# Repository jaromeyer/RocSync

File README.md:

# 🎥 RocSync
 
**Millisecond-Accurate Temporal Synchronization for Heterogeneous Camera Systems**

> *Jaro Meyer¹, Frédéric Giraud², Joschua Wüthrich¹, Marc Pollefeys¹, Philipp Fürnstahl², Lilian Calvet²*
>
> ¹ Department of Computer Science, ETH Zurich, Switzerland\
> ² Research in Orthopedic Computer Science, Balgrist University Hospital, University of Zurich, Switzerland

> [!WARNING]
> **This repository is deprecated and no longer maintained.**
> Development has moved to a new fork, which will continue to be updated:
> 👉 **[BAL-ROCS-BUT-COOL/RocSync](https://github.com/BAL-ROCS-BUT-COOL/RocSync)**

**RocSync**  is an open-source solution for millisecond-accurate temporal synchronization of multiple cameras. The core component is a 25x25 cm PCB featuring 100 dual LEDs (each consisting of a visible red LED and an infrared LED) arranged in a circle and 16 additional dual LEDs to display a binary counter. There is always exactly one illuminated LED in the circle and it advances one step every millisecond, while the binary display counts the number of complete rotations. The second part is a Python application that decodes images and videos of the device and provides exact timestamps (relative to the RocSync device's internal clock) for every frame. It supports synchronization of both standard RGB cameras (e.g., Kinect, GoPro, Canon) and specialized IR tracking cameras, such as the [Atracsys fusionTrack 500](https://atracsys.com/fusiontrack-500/), making it ideal for research and applications requiring high-precision multi-camera setups.

## Repository Structure

This repository contains three main sections, each with its own README:

- **`fw/`**: PlatformIO project for microcontroller firmware.
- **`hw/`**: KiCad files for PCB design and CAD models.
- **`misc/`**: IR marker geometry specifications.
- **`sw/`**: Python source code for computer vision processing.

## Getting Started

For detailed instructions on setting up and using RocSync, please refer to the README files in the respective sections.

## Citation
If you use RocSync in your research, please cite:
```
@Article{s26031036,
AUTHOR = {Meyer, Jaro and Giraud, Frédéric and Wüthrich, Joschua and Pollefeys, Marc and Fürnstahl, Philipp and Calvet, Lilian},
TITLE = {RocSync: Millisecond-Accurate Temporal Synchronization for Heterogeneous Camera Systems},
JOURNAL = {Sensors},
VOLUME = {26},
YEAR = {2026},
NUMBER = {3},
ARTICLE-NUMBER = {1036},
URL = {https://www.mdpi.com/1424-8220/26/3/1036},
PubMedID = {41682551},
ISSN = {1424-8220},
DOI = {10.3390/s26031036}
}
```

## Credits

- **Frédéric Giraud**: Creator of the initial prototype.
- **Lilian Calvet**: Conceptual designer.

Feel free to explore, contribute, and use RocSync in your projects!

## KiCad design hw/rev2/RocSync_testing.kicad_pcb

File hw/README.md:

# RocSync Hardware
This folder contains the KiCad project for the RocSync device, designed with JLCPCB manufacturing and assembly in mind. Fabrication files were generated using the [JLCPCB tools plugin](https://github.com/Bouni/kicad-jlcpcb-tools). The latest production files are available [here](rev2/jlcpcb/production_files/).

## Accuracy
Revision 1 likely experienced accuracy issues documented [here](https://github.com/nlouman/documentation_todos_nino/blob/main/rocsync/1_checking_rocsync_clock.md), though never confirmed against a known accurate reference. Revision 2 replaced the crystal with a high-precision TCXO to improve absolute accuracy. Testing against a u-blox NEO-M8N GPS timepulse output showed ~1.3 ppm drift over 24 hours, roughly consistent with the TCXO's specification. This equates to 1 ms drift every 13 minutes. 

For even better accuracy, consider dedicating an unused GPIO pin (e.g., OLED SDA or SCL) to feed a 1000 Hz timepulse signal directly from the GPS module into the microcontroller, using it as the clock source.

## Revision History
- **Rev1**: Initial design with 16-bit counter and crystal oscillator. Single-sided JLCPCB assembly with manual back-side soldering.
- **Rev2**: Improved design featuring a 20-bit counter, high-precision TCXO, 5-way button interface, and fifth corner LED for unambiguous orientation detection. Optimized for dual-sided assembly.

## Potential Improvements
- [ ] Decouple IR and visible LED brightness
- [ ] Address LED brightness degradation at low battery voltage (consider implementing a buck-boost converter)

## JLCPCB Ordering
1. Upload the **Gerber files** and let JLCPCB auto-populate all options.
2. Enable **PCB Assembly**, selecting **Standard PCBA** and **top side assembly**.
3. Upload the **BOM** and **POS files**.
4. Review the 3D preview and proceed to place your order.

## Mechanical BOM
| Part                                | Quantity | Source                                                              |
| ----------------------------------- | -------- | ------------------------------------------------------------------- |
| 604050 battery with PH2.0 connector | 1        | [Aliexpress](https://aliexpress.com/item/1005009787566737.html) or [Aliexpress](https://aliexpress.com/item/1005010639629430.html) |
| Handle                              | 1        | [3D printed](rev2/3d_models/handle.stl)                             |
| Cover                               | 1        | [3D printed](rev2/3d_models/top_cover.stl)                          |
| M3x10 screws                        | 4        | [Aliexpress](https://www.aliexpress.com/item/32850409234.html)      |
| M3 nuts                             | 4        | [Aliexpress](https://www.aliexpress.com/item/32977174437.html)      |
| Matte smoked film ~32x32 cm         | 1        | [Aliexpress](https://www.aliexpress.com/item/1005005636607163.html) |

## Assembly Instructions
> ⚠️ **Warning**: Verify battery polarity before turning on! The polarity of PH2.0 connectors may differ among battery manufacturers. The positive pin should be the one located closer to the center of the device. 

1. **Prepare the Film**  
   Cut a **30x30 cm square** from the matte smoked film. Place it with the **sticky side facing up** on a flat surface.

2. **Position the Faceplate**  
   Carefully center the **3D printed faceplate** on the film, ensuring the side with the **cutouts** that will later contact the PCB is facing up. If the film is curling, it can be helpful to have someone hold down the corners of the film while you position the faceplate.

3. **Create Center Flaps**  
   Use a cutter or knife to make an **X-shaped cut** in the center square hole of the film. Fold the resulting four flaps upwards and trim the tips, leaving a **2-3 cm strip**. Stick them to the faceplate, making sure to tension the film for a tight fit around the cutout.

4. **Clear Cutouts**  
   Cut away the film from the **cutouts** by slicing along their edges to detach the small film pieces. For the **top side** with **40 counter LEDs**, consider cutting the film into vertical strips between the LEDs and removing the sections covering the LEDs, rather than cutting out each hole individually.

5. **Attach the PCB**  
   Place the **PCB** facing down onto the prepared front plate, ensuring all LEDs are protruding through the cutouts. The PCB should fit snugly against the faceplate.

6. **Secure the PCB**  
    Cut away squares from the outer corners of the film to create flaps that can be folded around the PCB and adhered to its back. This will hold the PCB tightly against the faceplate. Make sure to firmly pull the film around the edge before sticking it down. It is easiest to start from the **middle** and work your way out to the corners, pulling the film tight each time before adhering a new section to the PCB.

7. **Attach the Handle**
   Use a cutter to poke holes through the film for the **four screws**. Attach the handle to the back of the PCB, ensuring the **battery cable** routes through the designated channel, and secure it with screws and nuts.

8. **Secure the Battery**  
   Adhere the battery to the back of the handle using **thin double-sided tape** to prevent it from falling out when the device is turned upside down. If the battery doesn't fit directly, you might have to fold its corners inwards to make it fit.

9.  **Connect the Battery and Power On**  
    Connect the battery to the PCB, ensuring the **correct polarity**. The positive pin should be the one closer to the center. When you turn on the power switch, the device should activate, and the LEDs will begin to blink.

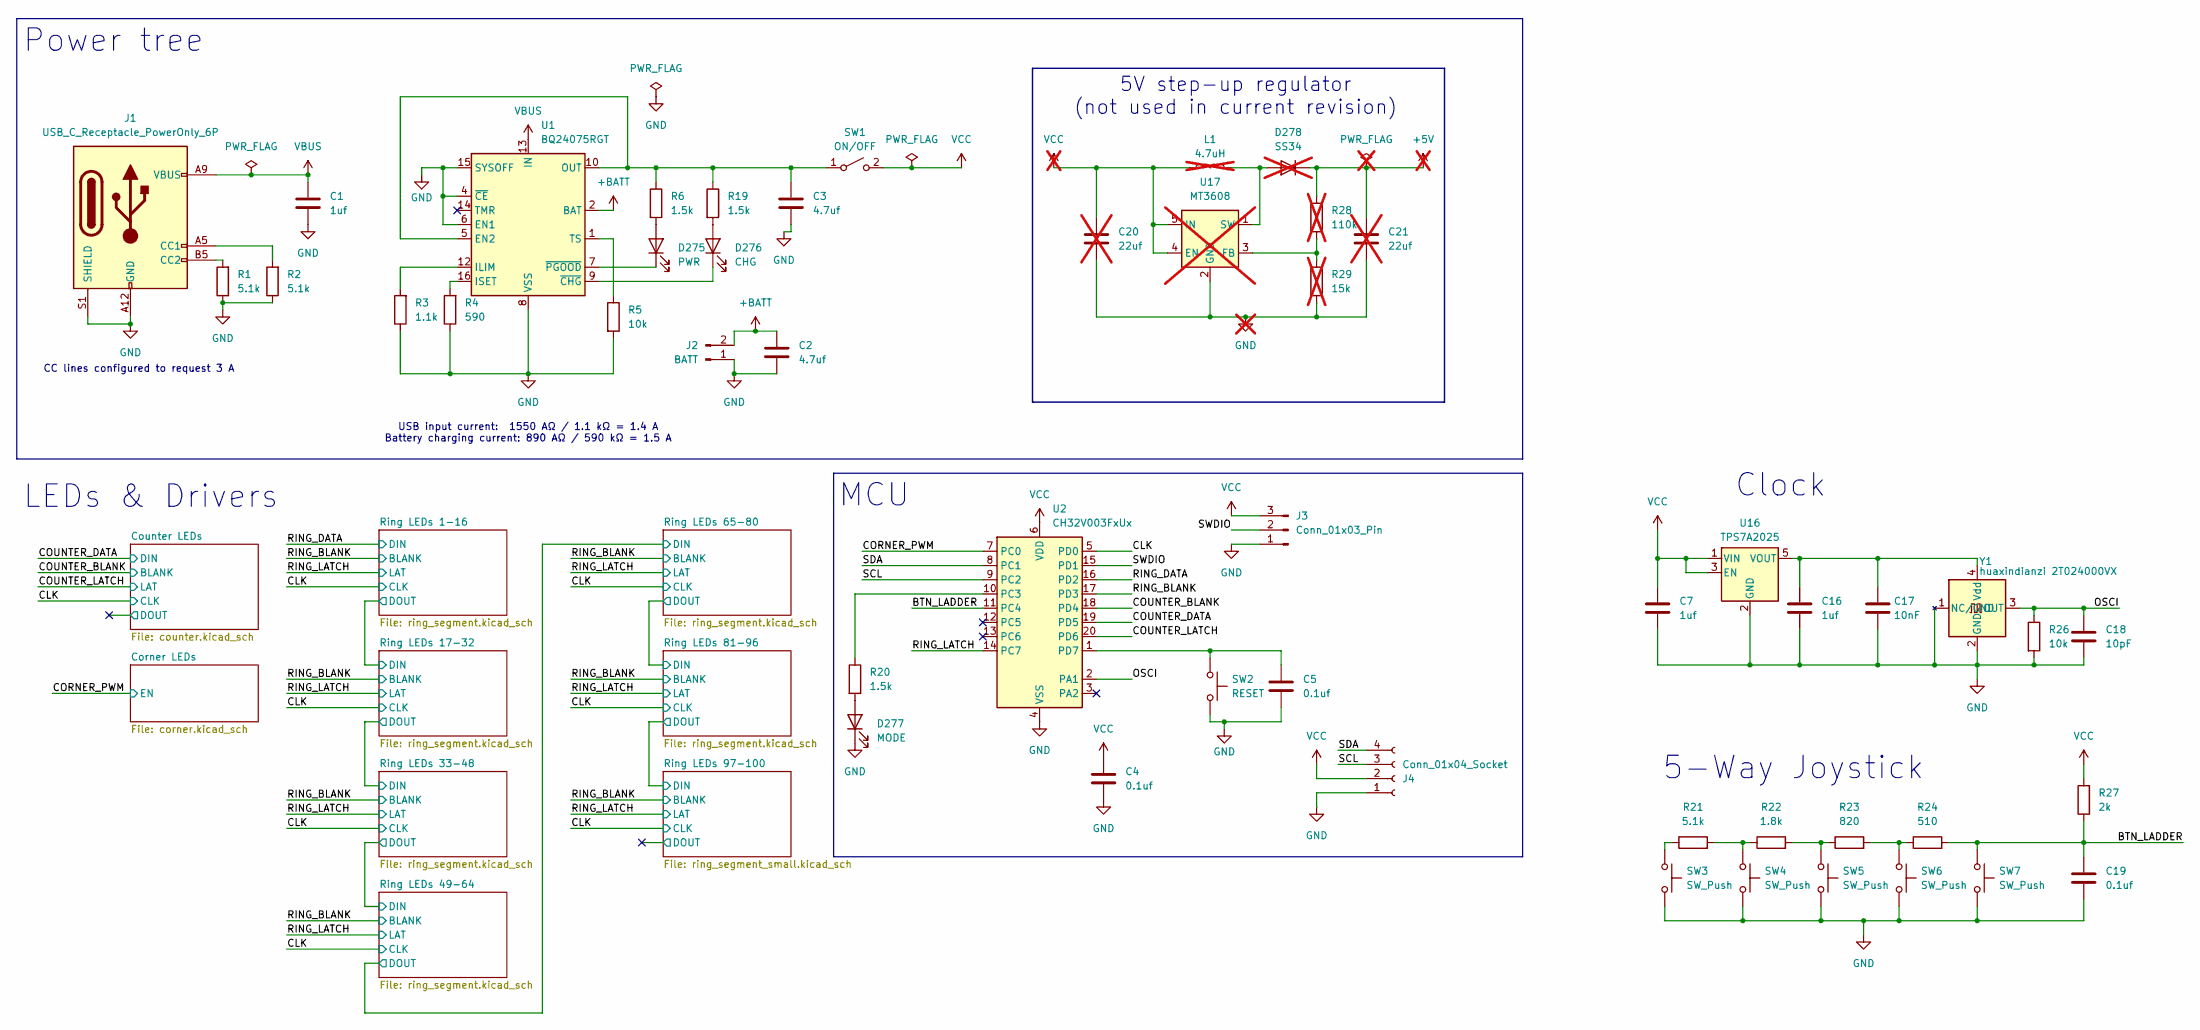
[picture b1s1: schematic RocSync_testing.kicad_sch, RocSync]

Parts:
C1, C7, C16: 1uf; C_0402_1005Metric
C2, C3: 4.7uf; C_0402_1005Metric
C4, C5, C19: 0.1uf; C_0402_1005Metric
C17: 10nF; C_0402_1005Metric
C18: 10pF; C_0402_1005Metric
C20, C21: 22uf; C_0805_2012Metric; not fitted
D275: PWR; LED_0603_1608Metric
D276: CHG; LED_0603_1608Metric
D277: MODE; LED_0603_1608Metric
D278: SS34; D_SMA; not fitted
J1: USB_C_Receptacle_PowerOnly_6P; USB_C_Receptacle_GCT_USB4115-03-C; MPN C3020049
J2: BATT; JST_PH_B2B-PH-K_1x02_P2.00mm_Vertical
J3: Conn_01x03_Pin; PinHeader_1x03_P2.54mm_Vertical
J4: Conn_01x04_Socket; PinHeader_1x04_P2.54mm_Vertical
L1: 4.7uH; L_6.3x6.3_H3; not fitted
R1, R2, R21: 5.1k; R_0402_1005Metric
R3: 1.1k; R_0402_1005Metric
R4: 590; R_0402_1005Metric
R5, R26: 10k; R_0402_1005Metric
R6, R19, R20: 1.5k; R_0402_1005Metric
R22: 1.8k; R_0402_1005Metric
R23: 820; R_0402_1005Metric
R24: 510; R_0402_1005Metric
R27: 2k; R_0402_1005Metric
R28: 110k; R_0402_1005Metric; not fitted
R29: 15k; R_0402_1005Metric; not fitted
SW1: ON/OFF; SW_CK_JS202011CQN_DPDT_Straight
SW2: RESET; SW_Push_1P1T_NO_6x6mm_H9.5mm
SW3, SW4, SW5, SW6, SW7: SW_Push; SW_Push_1P1T_NO_6x6mm_H9.5mm
U1: BQ24075RGT; VQFN-16-1EP_3x3mm_P0.5mm_EP1.68x1.68mm_ThermalVias
U2: CH32V003FxUx; QFN-20-1EP_3x3mm_P0.4mm_EP1.65x1.65mm_ThermalVias
U16: TPS7A2025; SOT-23-5
U17: MT3608; SOT-23-6; not fitted
Y1: huaxindianzi 2T024000VX; Oscillator_SMD_SeikoEpson_TG2520SMN-xxx-xxxxxx-4Pin_2.5x2.0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

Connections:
+BATT: C2.1, J2.2, U1.2 (BAT), U1.3 (BAT)
/BTN_LADDER: C19.1, R24.2, R27.1, SW7.1, U2.11 (PC4)
/CLK: U2.5 (PD0); also elsewhere on the board
/CORNER_PWM: U2.7 (PC0); also elsewhere on the board
/COUNTER_BLANK: U2.18 (PD4); also elsewhere on the board
/COUNTER_DATA: U2.19 (PD5); also elsewhere on the board
/COUNTER_LATCH: U2.20 (PD6); also elsewhere on the board
/OSCI: C18.1, R26.1, U2.2 (PA1), Y1.3 (OUT)
/RING_BLANK: U2.17 (PD3); also elsewhere on the board
/RING_DATA: U2.16 (PD2); also elsewhere on the board
/RING_LATCH: U2.14 (PC7); also elsewhere on the board
/SCL: J4.3, U2.9 (PC2)
/SDA: J4.4, U2.8 (PC1)
/SWDIO: J3.2, U2.15 (PD1)
GND: C1.2, C2.2, C3.2, C4.2, C5.2, C7.2, C16.2, C17.2, C18.2, C19.2, C20.2, C21.2, D277.1 (K), J1.A12 (GND), J1.B12 (GND), J1.S1 (SHIELD), J2.1, J3.1, J4.1, R1.1, R2.1, R3.1, R4.1, R5.2, R26.2, R29.2, SW2.2, SW3.2, SW4.2, SW5.2, SW6.2, SW7.2, U1.4 (~CE), U1.6 (EN1), U1.8 (VSS), U1.15 (SYSOFF), U1.17 (VSS), U2.4 (VSS), U2.21 (VSS), U16.2 (GND), U17.2 (GND), Y1.1 (NC/GND), Y1.2 (GND); also elsewhere on the board
unnamed: C21.1, D278.1 (K), R28.1
unnamed: D275.2 (A), R6.2
unnamed: D275.1 (K), U1.7 (~PGOOD)
unnamed: D276.2 (A), R19.2
unnamed: D276.1 (K), U1.9 (~CHG)
unnamed: D277.2 (A), R20.2
unnamed: D278.2 (A), L1.2, U17.1 (SW)
unnamed: J1.A5 (CC1), R2.2
unnamed: J1.B5 (CC2), R1.2
unnamed: R21.1, SW3.1
unnamed: R21.2, R22.1, SW4.1
unnamed: R22.2, R23.1, SW5.1
unnamed: R23.2, R24.1, SW6.1
unnamed: R28.2, R29.1, U17.3 (FB)
unnamed: C3.1, R6.1, R19.1, SW1.1 (A), U1.5 (EN2), U1.10 (OUT), U1.11 (OUT)
unnamed: R3.2, U1.12 (ILIM)
unnamed: R4.2, U1.16 (ISET)
unnamed: R5.1, U1.1 (TS)
unnamed: R20.1, U2.10 (PC3)
unnamed: C5.1, SW2.1, U2.1 (PD7)
unnamed: C16.1, C17.1, U16.5 (VOUT), Y1.4 (Vdd)
VBUS: C1.1, J1.A9 (VBUS), J1.B9 (VBUS), U1.13 (IN)
VCC: C4.1, C7.1, C20.1, J3.3, J4.2, L1.1, R27.2, SW1.2 (B), U2.6 (VDD), U16.1 (VIN), U16.3 (EN), U17.4 (EN), U17.5 (IN); also elsewhere on the board

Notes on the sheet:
USB input current: 1550 AΩ / 1.1 kΩ = 1.4 A Battery charging current: 890 AΩ / 590 kΩ = 1.5 A
5-Way Joystick
LEDs & Drivers
Clock
MCU
CC lines configured to request 3 A
Power tree
5V step-up regulator (not used in current revision)

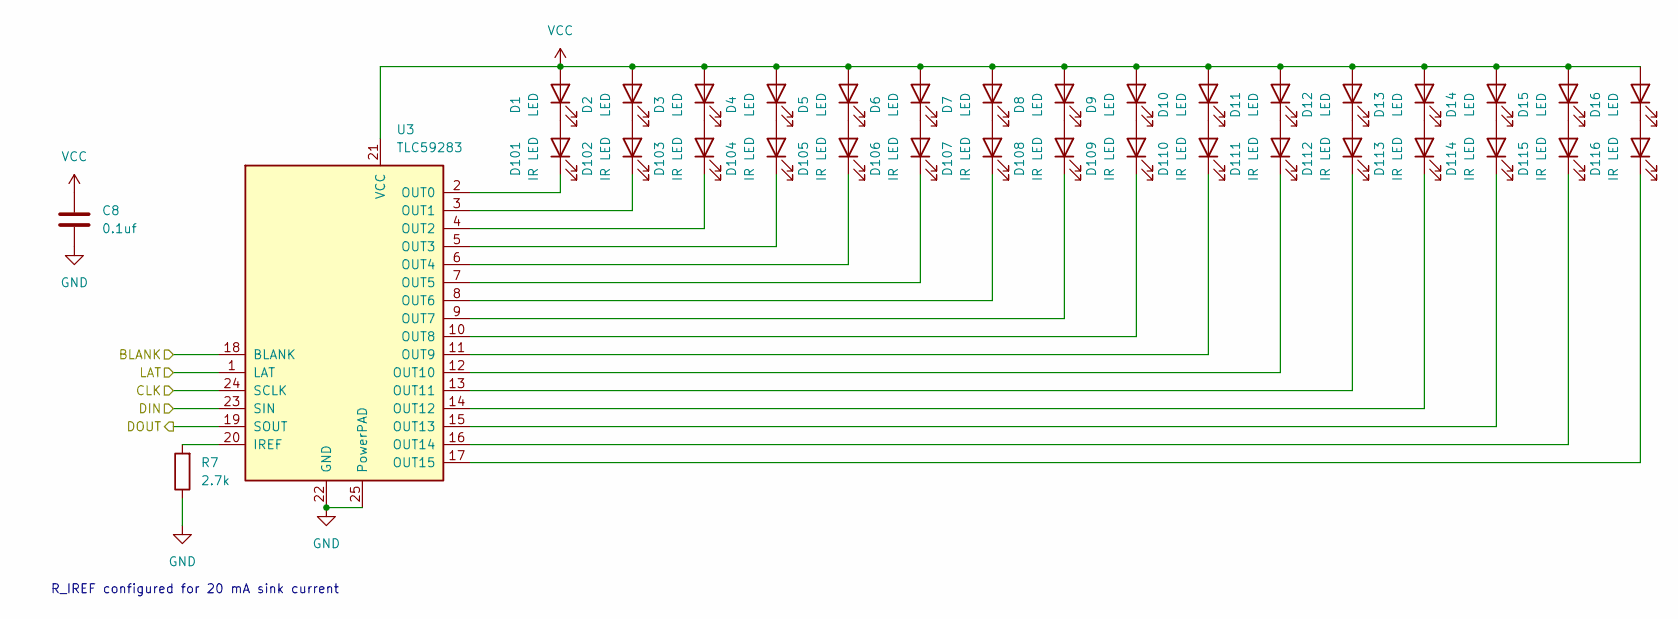
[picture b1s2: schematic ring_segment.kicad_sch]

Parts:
C8: 0.1uf; C_0402_1005Metric
D1, D2, D3, D4, D5, D6, D7, D8, D9, D10, D11, D12, D13, D14, D15, D16: LED; HL-A-3528
D101, D102, D103, D104, D105, D106, D107, D108, D109, D110, D111, D112, D113, D114, D115, D116: IR LED; XYC-HIR76C-LX4
R7: 2.7k; R_0402_1005Metric
U3: TLC59283; Texas_RGE0024C_VQFN-24-1EP_4x4mm_P0.5mm_EP2.1x2.1mm_Thermal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

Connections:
/CLK: U3.24 (SCLK); also elsewhere on the board
/RING_BLANK: U3.18 (BLANK); also elsewhere on the board
/RING_DATA: U3.23 (SIN); also elsewhere on the board
/RING_LATCH: U3.1 (LAT); also elsewhere on the board
/Ring LEDs 1-16/DOUT: U3.19 (SOUT); also elsewhere on the board
GND: C8.1, R7.1, U3.22 (GND), U3.25 (PowerPAD); also elsewhere on the board
unnamed: D1.1 (K), D101.2 (A)
unnamed: D10.1 (K), D110.2 (A)
unnamed: D11.1 (K), D111.2 (A)
unnamed: D101.1 (K), U3.2 (OUT0)
unnamed: D2.1 (K), D102.2 (A)
unnamed: D102.1 (K), U3.3 (OUT1)
unnamed: D3.1 (K), D103.2 (A)
unnamed: D103.1 (K), U3.4 (OUT2)
unnamed: D4.1 (K), D104.2 (A)
unnamed: D104.1 (K), U3.5 (OUT3)
unnamed: D5.1 (K), D105.2 (A)
unnamed: D105.1 (K), U3.6 (OUT4)
unnamed: D6.1 (K), D106.2 (A)
unnamed: D106.1 (K), U3.7 (OUT5)
unnamed: D7.1 (K), D107.2 (A)
unnamed: D107.1 (K), U3.8 (OUT6)
unnamed: D8.1 (K), D108.2 (A)
unnamed: D108.1 (K), U3.9 (OUT7)
unnamed: D9.1 (K), D109.2 (A)
unnamed: D109.1 (K), U3.10 (OUT8)
unnamed: D110.1 (K), U3.11 (OUT9)
unnamed: D111.1 (K), U3.12 (OUT10)
unnamed: D12.1 (K), D112.2 (A)
unnamed: D112.1 (K), U3.13 (OUT11)
unnamed: D13.1 (K), D113.2 (A)
unnamed: D113.1 (K), U3.14 (OUT12)
unnamed: D14.1 (K), D114.2 (A)
unnamed: D114.1 (K), U3.15 (OUT13)
unnamed: D15.1 (K), D115.2 (A)
unnamed: D115.1 (K), U3.16 (OUT14)
unnamed: D16.1 (K), D116.2 (A)
unnamed: D116.1 (K), U3.17 (OUT15)
unnamed: R7.2, U3.20 (IREF)
VCC: C8.2, D1.2 (A), D2.2 (A), D3.2 (A), D4.2 (A), D5.2 (A), D6.2 (A), D7.2 (A), D8.2 (A), D9.2 (A), D10.2 (A), D11.2 (A), D12.2 (A), D13.2 (A), D14.2 (A), D15.2 (A), D16.2 (A), U3.21 (VCC); also elsewhere on the board

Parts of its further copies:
C9, C10, C11, C12, C13: 0.1uf; C_0402_1005Metric
D17, D18, D19, D20, D21, D22, D23, D24, D25, D26, D27, D28, D29, D30, D31, D32, D33, D34, D35, D36, D37, D38, D39, D40, D41, D42, D43, D44, D45, D46, D47, D48, D49, D50, D51, D52, D53, D54, D55, D56, D57, D58, D59, D60, D61, D62, D63, D64, D65, D66, D67, D68, D69, D70, D71, D72, D73, D74, D75, D76, D77, D78, D79, D80, D81, D82, D83, D84, D85, D86, D87, D88, D89, D90, D91, D92, D93, D94, D95, D96: LED; HL-A-3528
D117, D118, D119, D120, D121, D122, D123, D124, D125, D126, D127, D128, D129, D130, D131, D132, D133, D134, D135, D136, D137, D138, D139, D140, D141, D142, D143, D144, D145, D146, D147, D148, D149, D150, D151, D152, D153, D154, D155, D156, D157, D158, D159, D160, D161, D162, D163, D164, D165, D166, D167, D168, D169, D170, D171, D172, D173, D174, D175, D176, D177, D178, D179, D180, D181, D182, D183, D184, D185, D186, D187, D188, D189, D190, D191, D192, D193, D194, D195, D196: IR LED; XYC-HIR76C-LX4
R8, R9, R10, R11, R12: 2.7k; R_0402_1005Metric
U4, U5, U6, U7, U8: TLC59283; Texas_RGE0024C_VQFN-24-1EP_4x4mm_P0.5mm_EP2.1x2.1mm_Thermal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

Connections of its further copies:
/CLK: U4.24 (SCLK), U5.24 (SCLK), U6.24 (SCLK), U7.24 (SCLK), U8.24 (SCLK); also elsewhere on the board
/RING_BLANK: U4.18 (BLANK), U5.18 (BLANK), U6.18 (BLANK), U7.18 (BLANK), U8.18 (BLANK); also elsewhere on the board
/RING_LATCH: U4.1 (LAT), U5.1 (LAT), U6.1 (LAT), U7.1 (LAT), U8.1 (LAT); also elsewhere on the board
/Ring LEDs 1-16/DOUT: U4.23 (SIN); also elsewhere on the board
/Ring LEDs 17-32/DOUT: U4.19 (SOUT), U5.23 (SIN)
/Ring LEDs 33-48/DOUT: U5.19 (SOUT), U6.23 (SIN)
/Ring LEDs 49-64/DOUT: U6.19 (SOUT), U7.23 (SIN)
/Ring LEDs 65-80/DOUT: U7.19 (SOUT), U8.23 (SIN)
/Ring LEDs 81-96/DOUT: U8.19 (SOUT); also elsewhere on the board
GND: C9.1, C10.1, C11.1, C12.1, C13.1, R8.1, R9.1, R10.1, R11.1, R12.1, U4.22 (GND), U4.25 (PowerPAD), U5.22 (GND), U5.25 (PowerPAD), U6.22 (GND), U6.25 (PowerPAD), U7.22 (GND), U7.25 (PowerPAD), U8.22 (GND), U8.25 (PowerPAD); also elsewhere on the board
unnamed: D17.1 (K), D117.2 (A)
unnamed: D117.1 (K), U4.2 (OUT0)
unnamed: D18.1 (K), D118.2 (A)
unnamed: D118.1 (K), U4.3 (OUT1)
unnamed: D19.1 (K), D119.2 (A)
unnamed: D119.1 (K), U4.4 (OUT2)
unnamed: D20.1 (K), D120.2 (A)
unnamed: D120.1 (K), U4.5 (OUT3)
unnamed: D21.1 (K), D121.2 (A)
unnamed: D121.1 (K), U4.6 (OUT4)
unnamed: D22.1 (K), D122.2 (A)
unnamed: D122.1 (K), U4.7 (OUT5)
unnamed: D23.1 (K), D123.2 (A)
unnamed: D123.1 (K), U4.8 (OUT6)
unnamed: D24.1 (K), D124.2 (A)
unnamed: D124.1 (K), U4.9 (OUT7)
unnamed: D25.1 (K), D125.2 (A)
unnamed: D125.1 (K), U4.10 (OUT8)
unnamed: D26.1 (K), D126.2 (A)
unnamed: D126.1 (K), U4.11 (OUT9)
unnamed: D27.1 (K), D127.2 (A)
unnamed: D127.1 (K), U4.12 (OUT10)
unnamed: D28.1 (K), D128.2 (A)
unnamed: D128.1 (K), U4.13 (OUT11)
unnamed: D29.1 (K), D129.2 (A)
unnamed: D129.1 (K), U4.14 (OUT12)
unnamed: D30.1 (K), D130.2 (A)
unnamed: D130.1 (K), U4.15 (OUT13)
unnamed: D31.1 (K), D131.2 (A)
unnamed: D131.1 (K), U4.16 (OUT14)
unnamed: D32.1 (K), D132.2 (A)
unnamed: D132.1 (K), U4.17 (OUT15)
unnamed: D33.1 (K), D133.2 (A)
unnamed: D133.1 (K), U5.2 (OUT0)
unnamed: D34.1 (K), D134.2 (A)
unnamed: D134.1 (K), U5.3 (OUT1)
unnamed: D35.1 (K), D135.2 (A)
unnamed: D135.1 (K), U5.4 (OUT2)
unnamed: D36.1 (K), D136.2 (A)
unnamed: D136.1 (K), U5.5 (OUT3)
unnamed: D37.1 (K), D137.2 (A)
unnamed: D137.1 (K), U5.6 (OUT4)
unnamed: D38.1 (K), D138.2 (A)
unnamed: D138.1 (K), U5.7 (OUT5)
unnamed: D39.1 (K), D139.2 (A)
unnamed: D139.1 (K), U5.8 (OUT6)
unnamed: D40.1 (K), D140.2 (A)
unnamed: D140.1 (K), U5.9 (OUT7)
unnamed: D41.1 (K), D141.2 (A)
unnamed: D141.1 (K), U5.10 (OUT8)
unnamed: D42.1 (K), D142.2 (A)
unnamed: D142.1 (K), U5.11 (OUT9)
unnamed: D43.1 (K), D143.2 (A)
unnamed: D143.1 (K), U5.12 (OUT10)
unnamed: D44.1 (K), D144.2 (A)
unnamed: D144.1 (K), U5.13 (OUT11)
unnamed: D45.1 (K), D145.2 (A)
unnamed: D145.1 (K), U5.14 (OUT12)
unnamed: D46.1 (K), D146.2 (A)
unnamed: D146.1 (K), U5.15 (OUT13)
unnamed: D47.1 (K), D147.2 (A)
unnamed: D147.1 (K), U5.16 (OUT14)
unnamed: D48.1 (K), D148.2 (A)
unnamed: D148.1 (K), U5.17 (OUT15)
unnamed: D49.1 (K), D149.2 (A)
unnamed: D149.1 (K), U6.2 (OUT0)
unnamed: D50.1 (K), D150.2 (A)
unnamed: D150.1 (K), U6.3 (OUT1)
unnamed: D51.1 (K), D151.2 (A)
unnamed: D151.1 (K), U6.4 (OUT2)
unnamed: D52.1 (K), D152.2 (A)
unnamed: D152.1 (K), U6.5 (OUT3)
unnamed: D53.1 (K), D153.2 (A)
unnamed: D153.1 (K), U6.6 (OUT4)
unnamed: D54.1 (K), D154.2 (A)
unnamed: D154.1 (K), U6.7 (OUT5)
unnamed: D55.1 (K), D155.2 (A)
unnamed: D155.1 (K), U6.8 (OUT6)
unnamed: D56.1 (K), D156.2 (A)
unnamed: D156.1 (K), U6.9 (OUT7)
unnamed: D57.1 (K), D157.2 (A)
unnamed: D157.1 (K), U6.10 (OUT8)
unnamed: D58.1 (K), D158.2 (A)
unnamed: D158.1 (K), U6.11 (OUT9)
unnamed: D59.1 (K), D159.2 (A)
unnamed: D159.1 (K), U6.12 (OUT10)
unnamed: D60.1 (K), D160.2 (A)
unnamed: D160.1 (K), U6.13 (OUT11)
unnamed: D61.1 (K), D161.2 (A)
unnamed: D161.1 (K), U6.14 (OUT12)
unnamed: D62.1 (K), D162.2 (A)
unnamed: D162.1 (K), U6.15 (OUT13)
unnamed: D63.1 (K), D163.2 (A)
unnamed: D163.1 (K), U6.16 (OUT14)
unnamed: D64.1 (K), D164.2 (A)
unnamed: D164.1 (K), U6.17 (OUT15)
unnamed: D65.1 (K), D165.2 (A)
unnamed: D165.1 (K), U7.2 (OUT0)
unnamed: D66.1 (K), D166.2 (A)
unnamed: D166.1 (K), U7.3 (OUT1)
unnamed: D67.1 (K), D167.2 (A)
unnamed: D167.1 (K), U7.4 (OUT2)
unnamed: D68.1 (K), D168.2 (A)
unnamed: D168.1 (K), U7.5 (OUT3)
unnamed: D69.1 (K), D169.2 (A)
unnamed: D169.1 (K), U7.6 (OUT4)
unnamed: D70.1 (K), D170.2 (A)
unnamed: D170.1 (K), U7.7 (OUT5)
unnamed: D71.1 (K), D171.2 (A)
unnamed: D171.1 (K), U7.8 (OUT6)
unnamed: D72.1 (K), D172.2 (A)
unnamed: D172.1 (K), U7.9 (OUT7)
unnamed: D73.1 (K), D173.2 (A)
unnamed: D173.1 (K), U7.10 (OUT8)
unnamed: D74.1 (K), D174.2 (A)
unnamed: D174.1 (K), U7.11 (OUT9)
unnamed: D75.1 (K), D175.2 (A)
unnamed: D175.1 (K), U7.12 (OUT10)
unnamed: D76.1 (K), D176.2 (A)
unnamed: D176.1 (K), U7.13 (OUT11)
unnamed: D77.1 (K), D177.2 (A)
unnamed: D177.1 (K), U7.14 (OUT12)
unnamed: D78.1 (K), D178.2 (A)
unnamed: D178.1 (K), U7.15 (OUT13)
unnamed: D79.1 (K), D179.2 (A)
unnamed: D179.1 (K), U7.16 (OUT14)
unnamed: D80.1 (K), D180.2 (A)
unnamed: D180.1 (K), U7.17 (OUT15)
unnamed: D81.1 (K), D181.2 (A)
unnamed: D181.1 (K), U8.2 (OUT0)
unnamed: D82.1 (K), D182.2 (A)
unnamed: D182.1 (K), U8.3 (OUT1)
unnamed: D83.1 (K), D183.2 (A)
unnamed: D183.1 (K), U8.4 (OUT2)
unnamed: D84.1 (K), D184.2 (A)
unnamed: D184.1 (K), U8.5 (OUT3)
unnamed: D85.1 (K), D185.2 (A)
unnamed: D185.1 (K), U8.6 (OUT4)
unnamed: D86.1 (K), D186.2 (A)
unnamed: D186.1 (K), U8.7 (OUT5)
unnamed: D87.1 (K), D187.2 (A)
unnamed: D187.1 (K), U8.8 (OUT6)
unnamed: D88.1 (K), D188.2 (A)
unnamed: D188.1 (K), U8.9 (OUT7)
unnamed: D89.1 (K), D189.2 (A)
unnamed: D189.1 (K), U8.10 (OUT8)
unnamed: D90.1 (K), D190.2 (A)
unnamed: D190.1 (K), U8.11 (OUT9)
unnamed: D91.1 (K), D191.2 (A)
unnamed: D191.1 (K), U8.12 (OUT10)
unnamed: D92.1 (K), D192.2 (A)
unnamed: D192.1 (K), U8.13 (OUT11)
unnamed: D93.1 (K), D193.2 (A)
unnamed: D193.1 (K), U8.14 (OUT12)
unnamed: D94.1 (K), D194.2 (A)
unnamed: D194.1 (K), U8.15 (OUT13)
unnamed: D95.1 (K), D195.2 (A)
unnamed: D195.1 (K), U8.16 (OUT14)
unnamed: D96.1 (K), D196.2 (A)
unnamed: D196.1 (K), U8.17 (OUT15)
unnamed: R8.2, U4.20 (IREF)
unnamed: R9.2, U5.20 (IREF)
unnamed: R10.2, U6.20 (IREF)
unnamed: R11.2, U7.20 (IREF)
unnamed: R12.2, U8.20 (IREF)
VCC: C9.2, C10.2, C11.2, C12.2, C13.2, D17.2 (A), D18.2 (A), D19.2 (A), D20.2 (A), D21.2 (A), D22.2 (A), D23.2 (A), D24.2 (A), D25.2 (A), D26.2 (A), D27.2 (A), D28.2 (A), D29.2 (A), D30.2 (A), D31.2 (A), D32.2 (A), D33.2 (A), D34.2 (A), D35.2 (A), D36.2 (A), D37.2 (A), D38.2 (A), D39.2 (A), D40.2 (A), D41.2 (A), D42.2 (A), D43.2 (A), D44.2 (A), D45.2 (A), D46.2 (A), D47.2 (A), D48.2 (A), D49.2 (A), D50.2 (A), D51.2 (A), D52.2 (A), D53.2 (A), D54.2 (A), D55.2 (A), D56.2 (A), D57.2 (A), D58.2 (A), D59.2 (A), D60.2 (A), D61.2 (A), D62.2 (A), D63.2 (A), D64.2 (A), D65.2 (A), D66.2 (A), D67.2 (A), D68.2 (A), D69.2 (A), D70.2 (A), D71.2 (A), D72.2 (A), D73.2 (A), D74.2 (A), D75.2 (A), D76.2 (A), D77.2 (A), D78.2 (A), D79.2 (A), D80.2 (A), D81.2 (A), D82.2 (A), D83.2 (A), D84.2 (A), D85.2 (A), D86.2 (A), D87.2 (A), D88.2 (A), D89.2 (A), D90.2 (A), D91.2 (A), D92.2 (A), D93.2 (A), D94.2 (A), D95.2 (A), D96.2 (A), U4.21 (VCC), U5.21 (VCC), U6.21 (VCC), U7.21 (VCC), U8.21 (VCC); also elsewhere on the board

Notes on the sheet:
R_IREF configured for 20 mA sink current

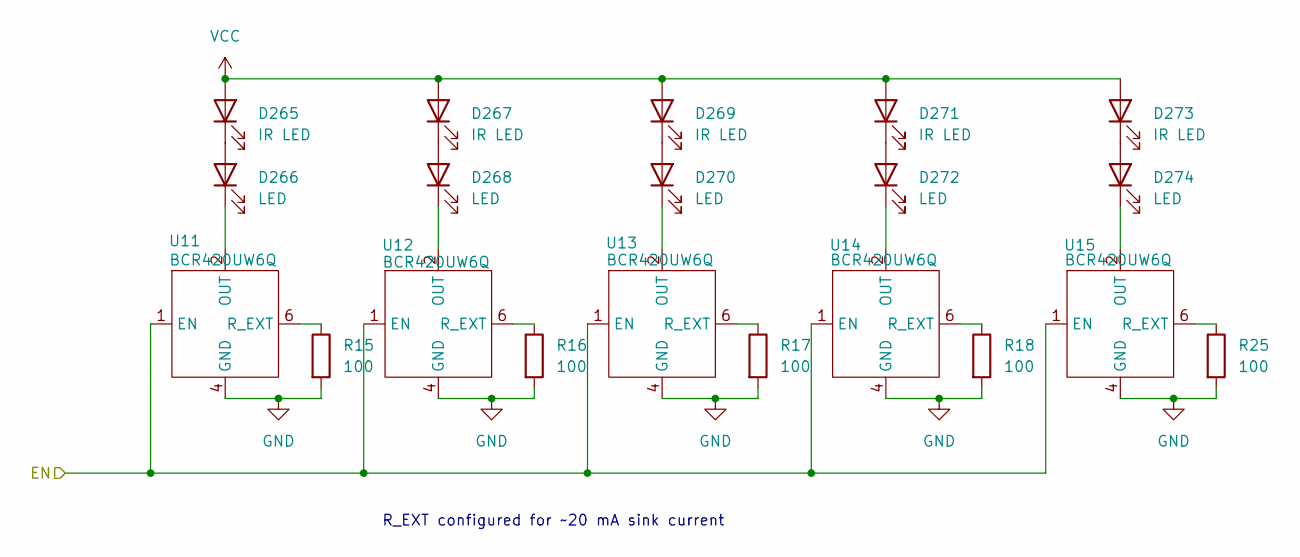
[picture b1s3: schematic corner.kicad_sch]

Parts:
D265, D267, D269, D271, D273: IR LED; XYC-HIR76C-LX4
D266, D268, D270, D272, D274: LED; HL-A-3528
R15, R16, R17, R18, R25: 100; R_0402_1005Metric
U11, U12, U13, U14, U15: BCR420UW6Q; SOT-23-6

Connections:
/CORNER_PWM: U11.1 (EN), U12.1 (EN), U13.1 (EN), U14.1 (EN), U15.1 (EN); also elsewhere on the board
GND: R15.2, R16.2, R17.2, R18.2, R25.2, U11.4 (GND), U12.4 (GND), U13.4 (GND), U14.4 (GND), U15.4 (GND); also elsewhere on the board
unnamed: D265.1 (K), D266.2 (A)
unnamed: D266.1 (K), U11.2 (OUT)
unnamed: D267.1 (K), D268.2 (A)
unnamed: D268.1 (K), U12.2 (OUT)
unnamed: D269.1 (K), D270.2 (A)
unnamed: D270.1 (K), U13.2 (OUT)
unnamed: D271.1 (K), D272.2 (A)
unnamed: D272.1 (K), U14.2 (OUT)
unnamed: D273.1 (K), D274.2 (A)
unnamed: D274.1 (K), U15.2 (OUT)
unnamed: R15.1, U11.6 (R_EXT)
unnamed: R16.1, U12.6 (R_EXT)
unnamed: R17.1, U13.6 (R_EXT)
unnamed: R18.1, U14.6 (R_EXT)
unnamed: R25.1, U15.6 (R_EXT)
VCC: D265.2 (A), D267.2 (A), D269.2 (A), D271.2 (A), D273.2 (A); also elsewhere on the board

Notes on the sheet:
R_EXT configured for ~20 mA sink current

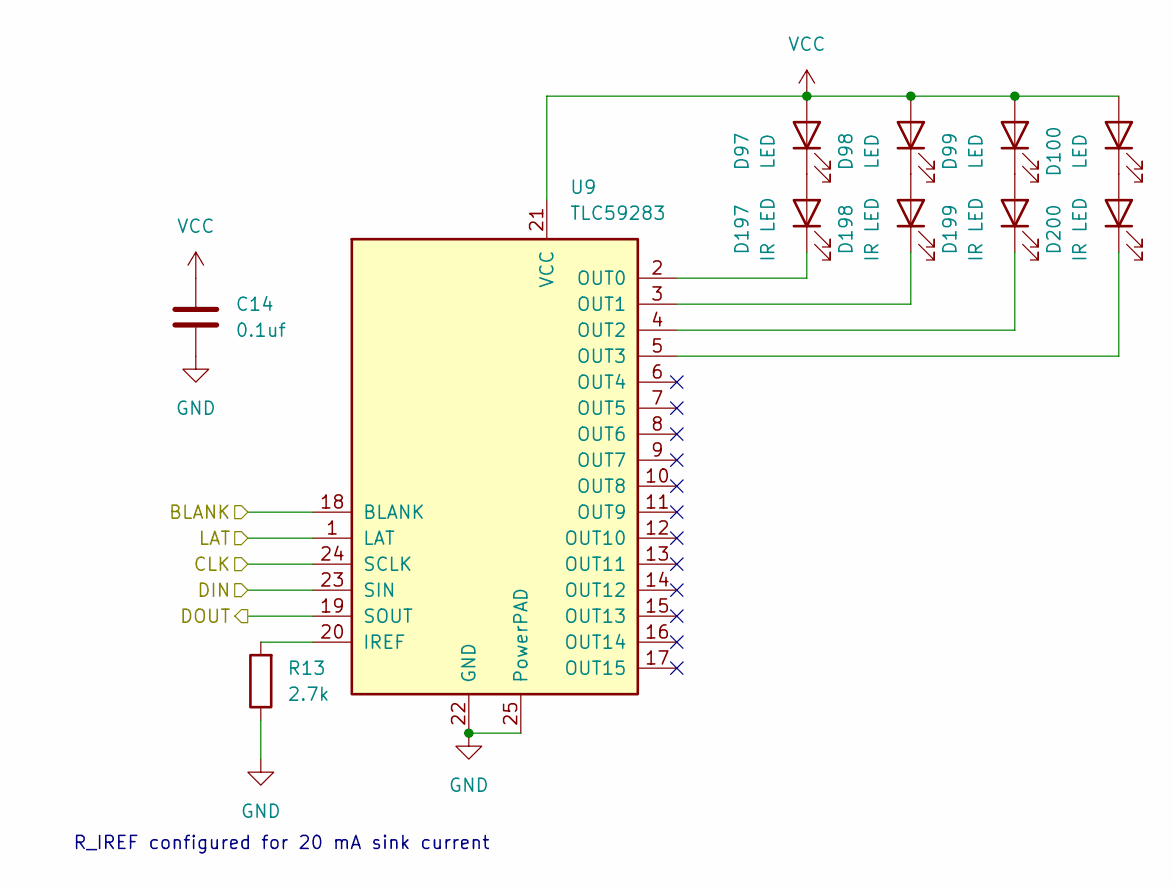
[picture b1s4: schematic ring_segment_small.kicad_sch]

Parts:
C14: 0.1uf; C_0402_1005Metric
D97, D98, D99, D100: LED; HL-A-3528
D197, D198, D199, D200: IR LED; XYC-HIR76C-LX4
R13: 2.7k; R_0402_1005Metric
U9: TLC59283; Texas_RGE0024C_VQFN-24-1EP_4x4mm_P0.5mm_EP2.1x2.1mm_Thermal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

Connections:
/CLK: U9.24 (SCLK); also elsewhere on the board
/RING_BLANK: U9.18 (BLANK); also elsewhere on the board
/RING_LATCH: U9.1 (LAT); also elsewhere on the board
/Ring LEDs 81-96/DOUT: U9.23 (SIN); also elsewhere on the board
/Ring LEDs 97-100/DOUT: U9.19 (SOUT)
GND: C14.2, R13.1, U9.22 (GND), U9.25 (PowerPAD); also elsewhere on the board
unnamed: D100.1 (K), D200.2 (A)
unnamed: D97.1 (K), D197.2 (A)
unnamed: D197.1 (K), U9.2 (OUT0)
unnamed: D98.1 (K), D198.2 (A)
unnamed: D198.1 (K), U9.3 (OUT1)
unnamed: D99.1 (K), D199.2 (A)
unnamed: D199.1 (K), U9.4 (OUT2)
unnamed: D200.1 (K), U9.5 (OUT3)
unnamed: R13.2, U9.20 (IREF)
VCC: C14.1, D97.2 (A), D98.2 (A), D99.2 (A), D100.2 (A), U9.21 (VCC); also elsewhere on the board

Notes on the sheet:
R_IREF configured for 20 mA sink current

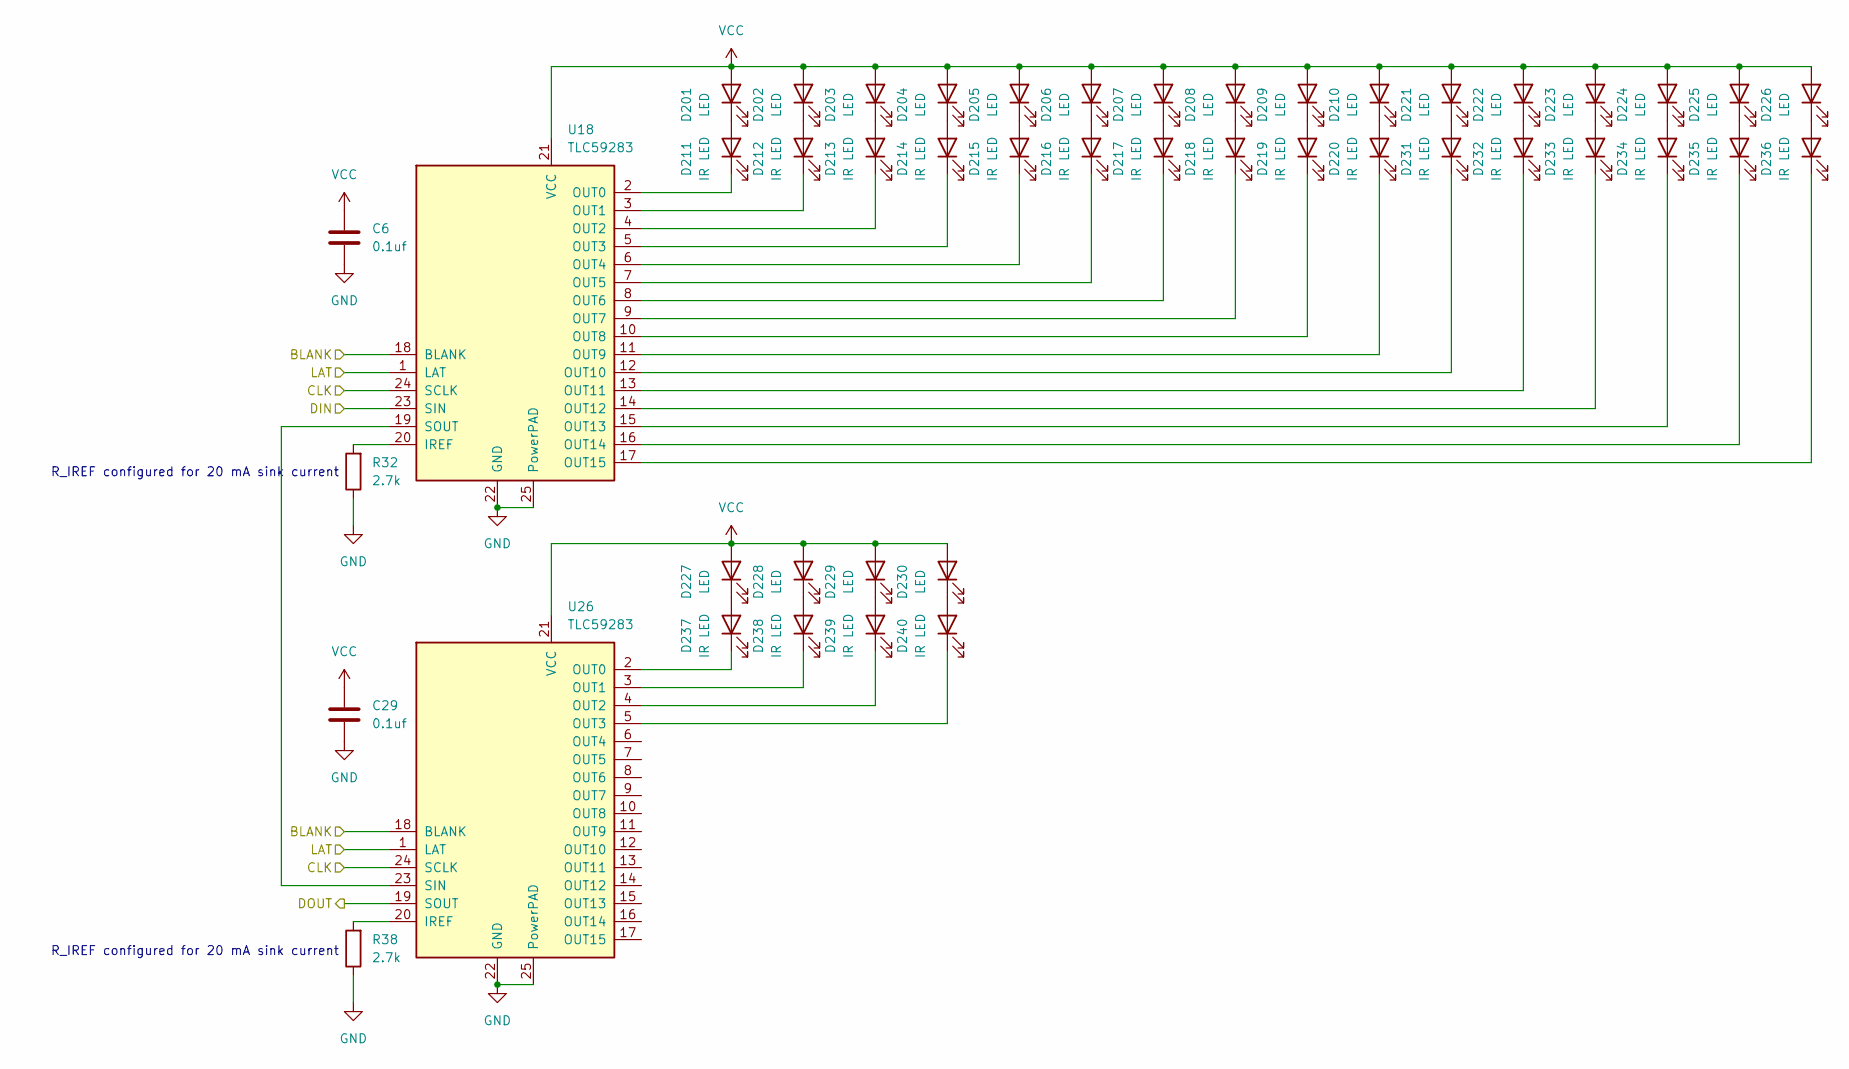
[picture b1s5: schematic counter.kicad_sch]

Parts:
C6, C29: 0.1uf; C_0402_1005Metric
D201, D202, D203, D204, D205, D206, D207, D208, D209, D210, D221, D222, D223, D224, D225, D226, D227, D228, D229, D230: LED; HL-A-3528
D211, D212, D213, D214, D215, D216, D217, D218, D219, D220, D231, D232, D233, D234, D235, D236, D237, D238, D239, D240: IR LED; XYC-HIR76C-LX4
R32, R38: 2.7k; R_0402_1005Metric
U18, U26: TLC59283; Texas_RGE0024C_VQFN-24-1EP_4x4mm_P0.5mm_EP2.1x2.1mm_Thermal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

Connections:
/CLK: U18.24 (SCLK), U26.24 (SCLK); also elsewhere on the board
/COUNTER_BLANK: U18.18 (BLANK), U26.18 (BLANK); also elsewhere on the board
/COUNTER_DATA: U18.23 (SIN); also elsewhere on the board
/COUNTER_LATCH: U18.1 (LAT), U26.1 (LAT); also elsewhere on the board
/Counter LEDs/DOUT: U26.19 (SOUT)
GND: C6.1, C29.1, R32.1, R38.1, U18.22 (GND), U18.25 (PowerPAD), U26.22 (GND), U26.25 (PowerPAD); also elsewhere on the board
unnamed: D201.1 (K), D211.2 (A)
unnamed: D202.1 (K), D212.2 (A)
unnamed: D203.1 (K), D213.2 (A)
unnamed: D204.1 (K), D214.2 (A)
unnamed: D205.1 (K), D215.2 (A)
unnamed: D206.1 (K), D216.2 (A)
unnamed: D207.1 (K), D217.2 (A)
unnamed: D208.1 (K), D218.2 (A)
unnamed: D209.1 (K), D219.2 (A)
unnamed: D210.1 (K), D220.2 (A)
unnamed: D211.1 (K), U18.2 (OUT0)
unnamed: D212.1 (K), U18.3 (OUT1)
unnamed: D213.1 (K), U18.4 (OUT2)
unnamed: D214.1 (K), U18.5 (OUT3)
unnamed: D215.1 (K), U18.6 (OUT4)
unnamed: D216.1 (K), U18.7 (OUT5)
unnamed: D217.1 (K), U18.8 (OUT6)
unnamed: D218.1 (K), U18.9 (OUT7)
unnamed: D219.1 (K), U18.10 (OUT8)
unnamed: D220.1 (K), U18.11 (OUT9)
unnamed: D221.1 (K), D231.2 (A)
unnamed: D222.1 (K), D232.2 (A)
unnamed: D223.1 (K), D233.2 (A)
unnamed: D224.1 (K), D234.2 (A)
unnamed: D225.1 (K), D235.2 (A)
unnamed: D226.1 (K), D236.2 (A)
unnamed: D227.1 (K), D237.2 (A)
unnamed: D228.1 (K), D238.2 (A)
unnamed: D229.1 (K), D239.2 (A)
unnamed: D230.1 (K), D240.2 (A)
unnamed: D231.1 (K), U18.12 (OUT10)
unnamed: D232.1 (K), U18.13 (OUT11)
unnamed: D233.1 (K), U18.14 (OUT12)
unnamed: D234.1 (K), U18.15 (OUT13)
unnamed: D235.1 (K), U18.16 (OUT14)
unnamed: D236.1 (K), U18.17 (OUT15)
unnamed: D237.1 (K), U26.2 (OUT0)
unnamed: D238.1 (K), U26.3 (OUT1)
unnamed: D239.1 (K), U26.4 (OUT2)
unnamed: D240.1 (K), U26.5 (OUT3)
unnamed: R32.2, U18.20 (IREF)
unnamed: U18.19 (SOUT), U26.23 (SIN)
unnamed: R38.2, U26.20 (IREF)
VCC: C6.2, C29.2, D201.2 (A), D202.2 (A), D203.2 (A), D204.2 (A), D205.2 (A), D206.2 (A), D207.2 (A), D208.2 (A), D209.2 (A), D210.2 (A), D221.2 (A), D222.2 (A), D223.2 (A), D224.2 (A), D225.2 (A), D226.2 (A), D227.2 (A), D228.2 (A), D229.2 (A), D230.2 (A), U18.21 (VCC), U26.21 (VCC); also elsewhere on the board

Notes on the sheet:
R_IREF configured for 20 mA sink current

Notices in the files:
README.md:
License: MPL-2.0
